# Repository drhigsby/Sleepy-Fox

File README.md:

# Sleepy-Fox

Full Gallery: https://imgur.com/gallery/EHu3umQ

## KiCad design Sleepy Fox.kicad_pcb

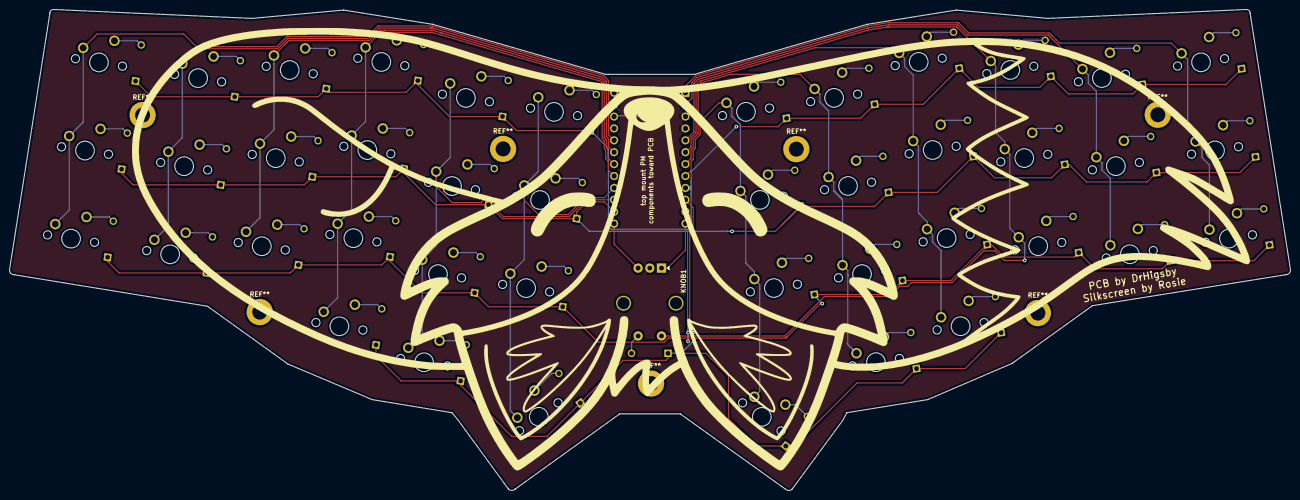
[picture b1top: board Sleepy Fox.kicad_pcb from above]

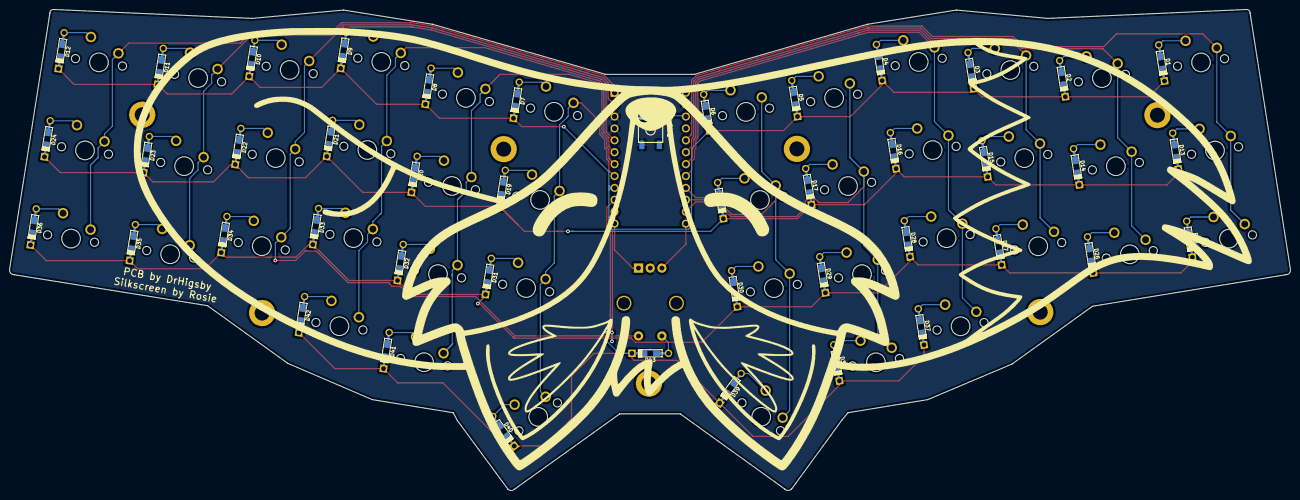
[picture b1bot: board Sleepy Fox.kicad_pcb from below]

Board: 2 copper layers, 273.6 x 102.7 mm, 88 parts (2 on the bottom side), 63 nets.

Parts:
D1, D2, D3, D4, D5, D6, D7, D8, D9, D10, D11, D12, D13, D14, D15, D16, D17, D18, D19, D20, D21, D22, D23, D24, D25, D26, D27, D28, D29, D30, D31, D32, D33, D34, D35, D36, D37, D38, D39, D40, D41, D42, D43: D_Small; Diode-Hybrid-Back
KNOB1: Rotary_Encoder_Switch; RotaryEncoder_Alps_EC11E-Switch_Vertical_H20mm_CircularMoun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
MX1, MX12, MX13, MX24, MX25, MX36: MX-NoLED; MXOnly-1.25U-NoLED
MX2, MX3, MX4, MX5, MX6, MX7, MX8, MX9, MX10, MX11, MX14, MX15, MX16, MX17, MX18, MX19, MX20, MX21, MX22, MX23, MX26, MX27, MX28, MX29, MX30, MX31, MX32, MX33, MX34, MX35, MX37, MX38, MX41, MX42: MX-NoLED; MXOnly-1U-NoLED
MX39, MX40: MX-NoLED; MXOnly-1.5U-NoLED
SW1: SW_Push; SKQGADE010
U1: ProMicro; ArduinoProMicro

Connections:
C1: MX1.1, MX13.1, MX25.1, U1.20
C2: MX2.1, MX14.1, MX26.1, U1.19
C3: MX3.1, MX15.1, MX27.1, U1.18
C4: MX4.1, MX16.1, MX28.1, MX37.1, U1.17
C5: MX5.1, MX17.1, MX29.1, MX38.1, U1.15
C6: MX6.1, MX18.1, MX30.1, MX39.1, U1.16
C7: MX7.1, MX19.1, MX31.1, MX40.1, U1.8
C8: MX8.1, MX20.1, MX32.1, MX41.1, U1.7
C9: MX9.1, MX21.1, MX33.1, MX42.1, U1.6
C10: KNOB1.S2, MX10.1, MX22.1, MX34.1, U1.5
C11: MX11.1, MX23.1, MX35.1, U1.2
C12: MX12.1, MX24.1, MX36.1, U1.1
GND: KNOB1.C, SW1.2, U1.3, U1.4, U1.23
unnamed: D1.2, MX1.2
unnamed: D2.2, MX2.2
unnamed: D3.2, MX3.2
unnamed: D4.2, MX4.2
unnamed: D5.2, MX5.2
unnamed: D6.2, MX6.2
unnamed: D7.2, MX7.2
unnamed: D8.2, MX8.2
unnamed: D9.2, MX9.2
unnamed: D10.2, MX10.2
unnamed: D11.2, MX11.2
unnamed: D12.2, MX12.2
unnamed: D13.2, MX13.2
unnamed: D14.2, MX14.2
unnamed: D15.2, MX15.2
unnamed: D16.2, MX16.2
unnamed: D17.2, MX17.2
unnamed: D18.2, MX18.2
unnamed: D19.2, MX19.2
unnamed: D20.2, MX20.2
unnamed: D21.2, MX21.2
unnamed: D22.2, MX22.2
unnamed: D23.2, MX23.2
unnamed: D24.2, MX24.2
unnamed: D25.2, MX25.2
unnamed: D26.2, MX26.2
unnamed: D27.2, MX27.2
unnamed: D28.2, MX28.2
unnamed: D29.2, MX29.2
unnamed: D30.2, MX30.2
unnamed: D31.2, MX31.2
unnamed: D32.2, MX32.2
unnamed: D33.2, MX33.2
unnamed: D34.2, MX34.2
unnamed: D35.2, MX35.2
unnamed: D36.2, MX36.2
unnamed: D37.2, MX37.2
unnamed: D38.2, MX38.2
unnamed: D39.2, MX39.2
unnamed: D40.2, MX40.2
unnamed: D41.2, MX41.2
unnamed: D42.2, MX42.2
unnamed: D43.2, KNOB1.S1
PM1: KNOB1.A, U1.12
PM2: KNOB1.B, U1.13
R1: D1.1, D2.1, D3.1, D4.1, D5.1, D6.1, D7.1, D8.1, D9.1, D10.1, D11.1, D12.1, U1.9
R2: D13.1, D14.1, D15.1, D16.1, D17.1, D18.1, D19.1, D20.1, D21.1, D22.1, D23.1, D24.1, U1.14
R3: D25.1, D26.1, D27.1, D28.1, D29.1, D30.1, D31.1, D32.1, D33.1, D34.1, D35.1, D36.1, U1.11
R4: D37.1, D38.1, D39.1, D40.1, D41.1, D42.1, D43.1, U1.10
RST: SW1.1, U1.22

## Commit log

2021-06-06 Lots of updates
    Lots of updates
2021-06-06 removing some unnecessary things
2021-06-14 plate updates
2021-06-17 removed unnecessary file
2021-06-17 repo cleanup
2022-03-24 updates
    big updates for firmware
2022-03-24 updates to readme
